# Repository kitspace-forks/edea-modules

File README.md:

# EDeA Test Modules

This is a collection of official modules to try out the functionality of EDeA.
The modules are provided on a best-effort basis and will be documented as verified
if and when they have been used in production boards.

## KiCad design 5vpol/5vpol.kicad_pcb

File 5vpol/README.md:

# 16-V Input 3-A Output Point-of-Load with TPS62135

## Overview

This design is based around the Texas Instruments TPS62135 converter.  
[IC Datasheet](https://www.ti.com/lit/ds/symlink/tps62135.pdf).
For layout, see the .kicad_pcb file in the repository.

## Use

Connect the input side to the power source, and the output side to the load. The converter powers on automatically above 3V input. Output is programmed to 5.0 volt, can be changed by replacing R2 and/or R3. Reference voltage is 0.7 V. Supported input voltage is around 16 V max., above which the D1 TVS diode will start to clamp. You can remove this to increase maximum input voltage to 18V abs max, but then you should avoid hot-plugging the board.

You can shut down the converter while input power is present: Pull EN input low. The EN pin is pulled up on-board to VIN with 10kOhm, therefore the circuit you use to discharge EN must withstand the maximum VIN you plan to apply.

Alternatively, you can disconnect the input.

To achieve 20-ish uA standby current, remove the output indicator LED D2 or its series resistor R6.

This DC/DC can run in 100% duty cycle mode, when the input voltage is lower or equals to the set output voltage.

## Properties

|                          Specifications |                                                                    |
|----------------------------------------:|--------------------------------------------------------------------|
|                             Dimensions: | 25x42x3mm (without pin headers)                                    |
|                                   Mass: | 3.3g                                                               |
|                          Mounting Hole: | M3 at (-6;-4)mm from bottom right corner                           |
|                          Input Voltage: | 3V - 16V                                                           |
|                         Output Voltage: | 5.0V (default)<br>Optionally between 0.8V and 12V                  |
|             Internal Reference Voltage: | 0.7V                                                               |
|                          Output Ripple: | 45mVpp with no load<br>30mVpp in Continuous Conduction Mode        |
|                         Output Current: | 4A peak<br>3.4A continuous                                         |
|                     Maximum Duty Cylce: | 100%                                                               |
|                            Power Stage: | Synchronous buck with nMOS switches                                |
|             Overtemperature Protection: | Yes, at 160 degrees Celsius, with 20 dC hysteresis                 |
|               Short Circuit Protection: | Yes, at 6A                                                         |
|              Fixed Switching Frequency: | No. (default) In Continuous Conduction Mode fSW is approx. 2.5 MHz <br> Yes (pseudo-static around 2.5 MHz) by pulling MODE pin high (VIN tolerant) |
|                             Soft Start: | 25ms, programmed by C3                                             |
| Transient Input Overvoltage Protection: | Yes, with on-board TVS diode                                       |
|          Output Overvoltage Protection: | No.                                                                |
|                       Hot-Plug Capable: | Yes.                                                               |
|                          Soft Shutdown: | Yes (by pulling EN pin low)                                        |
|                    Output ON Indicator: | Yes. (pink LED)                                                    |
|                      Power Good Output: | Yes.                                                               |
|                                   RoHS: | Yes, plus tantalum-free.                                           |

## Test report

I spent half a year validating this IC design before it was released to the market, and it is very robust. The only way to kill it is through overvoltage on its input or its output (or maybe using the wrong inductor and saturating it, but I have not tried that; it still works down to 0.7 uH).

Current limit is robust, and it also limits negative current when run in FPWM mode (MODE=high, see JP1) to around 1A. You can use it as a rudimentary bidirectional buck-boost if you so please!

You can even use it as an inverting buck-boost converter! (connect GND to the pin labeled VOUT, VIN is VIN, GND is -Vout) Mind that in this setup Vin+abs(Vout) still can't be higher than 17V!

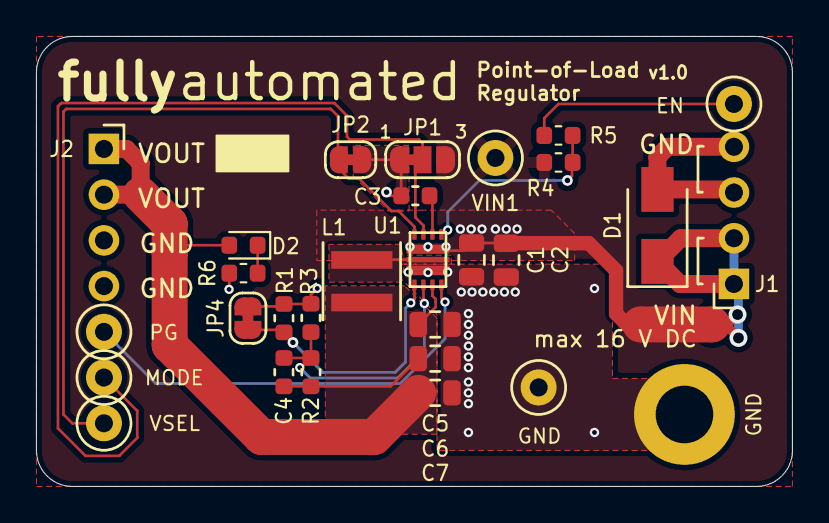
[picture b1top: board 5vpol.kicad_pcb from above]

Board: 2 copper layers, 42.0 x 25.0 mm, 31 parts (1 on the bottom side), 14 nets.

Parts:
C1, C2: 2.2uF/25V; C_0805_2012Metric
C3: 100nF/25V; C_0603_1608Metric
C4: 22pF/50V; C_0603_1608Metric
C5, C6, C7: 10uF/6.3V; C_0805_2012Metric
D1: SMAJ15A-13-F; D_SMA
D2: LED_Small_ALT; LED_0603_1608Metric
EN: EN; TestPoint_Loop_D1.80mm_Drill1.0mm_Beaded
G1: Fully_Automated_Logo; fully_automated_logo_soldermask
H1: MountingHole_Pad; MountingHole_3.2mm_M3_DIN965_Pad
J1: IN; PinSocket_1x04_P2.54mm_Horizontal
J2: OUT; PinSocket_1x04_P2.54mm_Horizontal
JP1: SolderJumper_3_Bridged12; SolderJumper-3_P1.3mm_Bridged12_RoundedPad1.0x1.5mm_NumberL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
JP2, JP4: SolderJumper_2_Bridged; SolderJumper-2_P1.3mm_Bridged_RoundedPad1.0x1.5mm
L1: XGL4020-102ME_; L_Coilcraft_XxL4020
MODE1: MODE; TestPoint_Loop_D1.80mm_Drill1.0mm_Beaded
NT1: Net-Tie_2; NetTie-2_SMD_Pad2.0mm
PG1: PG; TestPoint_Loop_D1.80mm_Drill1.0mm_Beaded
R1: dnp; R_0603_1608Metric
R2: 240k; R_0603_1608Metric
R3: 39k; R_0603_1608Metric
R4: 10k; R_0603_1608Metric
R5: 100; R_0603_1608Metric
R6: 2k2; R_0603_1608Metric
TP1: GND; TestPoint_Loop_D1.80mm_Drill1.0mm_Beaded
U1: TPS62135; RGX_TI_VQFN-HR11
VIN1: VIN; TestPoint_Loop_D1.80mm_Drill1.0mm_Beaded
VSEL1: VSEL; TestPoint_Loop_D1.80mm_Drill1.0mm_Beaded

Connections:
+5V: C4.1, C5.1, C6.1, C7.1, D2.2, J2.1, J2.2, L1.2, R2.1, U1.6
/TPS62135 Power Supply/FB: C4.2, R2.2, R3.1, U1.5
/TPS62135 Power Supply/MODE: JP1.2, MODE1.1, U1.10
/TPS62135 Power Supply/PGOOD: PG1.1, U1.7
/TPS62135 Power Supply/SW: L1.1, U1.2
GND: C1.2, C2.2, C3.2, C5.2, C6.2, C7.2, D1.2, H1.1, J1.3, J1.4, J2.3, J2.4, JP1.1, JP2.1, JP4.2, R1.2, R3.2, R6.2, TP1.1, U1.3
unnamed: C1.1, C2.1, JP1.3, NT1.2, R4.2, U1.1, VIN1.1
unnamed: C3.1, U1.9
unnamed: D2.1, R6.1
unnamed: EN.1, R5.1
unnamed: JP2.2, U1.11, VSEL1.1
unnamed: JP4.1, R1.1, U1.4
unnamed: R4.1, R5.2, U1.8
VBUS: D1.1, J1.1, J1.2, NT1.1

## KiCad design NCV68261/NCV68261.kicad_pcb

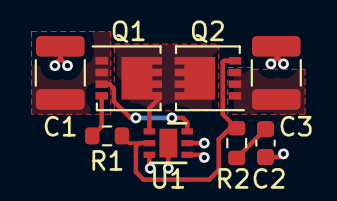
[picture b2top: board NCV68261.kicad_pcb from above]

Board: 2 copper layers, 8 parts (0 on the bottom side), 7 nets.

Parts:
C1, C3: 10uF/63V; C_1210_3225Metric
C2: 1nF; C_0603_1608Metric
Q1, Q2: DMT6007LFG-7; Diodes_PowerDI3333-8
R1, R2: 10R; R_0603_1608Metric
U1: NCV68261; DFN-6-1EP_2x2mm_P0.65mm_EP1x1.6mm

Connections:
/V_{BUS}: C1.1, Q1.1 (S), Q1.2 (S), Q1.3 (S), U1.6 (IN)
/V_{PROT}: C3.1, Q2.1 (S), Q2.2 (S), Q2.3 (S)
GND: C1.2, C2.1, C3.2, U1.3 (D), U1.5 (GND), U1.7
unnamed: C2.2, R2.2
unnamed: Q1.4 (G), R1.1
unnamed: Q1.5 (D), Q2.5 (D), U1.1 (S)
unnamed: Q2.4 (G), R1.2, R2.1, U1.2 (G)

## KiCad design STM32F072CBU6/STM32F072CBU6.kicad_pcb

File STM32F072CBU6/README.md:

# STM32CBU6

This module provides the STM32F072 in a 48-Pin VQFN package.

## Datasheets

- [STM32F072CB](https://www.st.com/resource/en/datasheet/stm32f072cb.pdf)
- [Reference Manual](https://www.st.com/resource/en/reference_manual/dm00031936-stm32f0x1stm32f0x2stm32f0x8-advanced-armbased-32bit-mcus-stmicroelectronics.pdf)

## Routing

No special assumptions, except for the existance of a Ground-plane, were made. The 3V3 rail was routed
without a 3V3 plane in mind in case this gets used in a more constrained setup.

## Debug Connector

The footprint for a TC2030 connector is present for debugging-purposes.

## JLC Compatible

All parts, except the STM32F072 are basic parts and have been choosen to be compatible
with the Microcontroller.

## Tolerances, Traces & Vias

Trace widths, Vias and spacing are compatible with 2oz outer layer on with common tolerances.
If lower tolerances are available, the traces and caps can be moved around still to make it
a bit more compact.

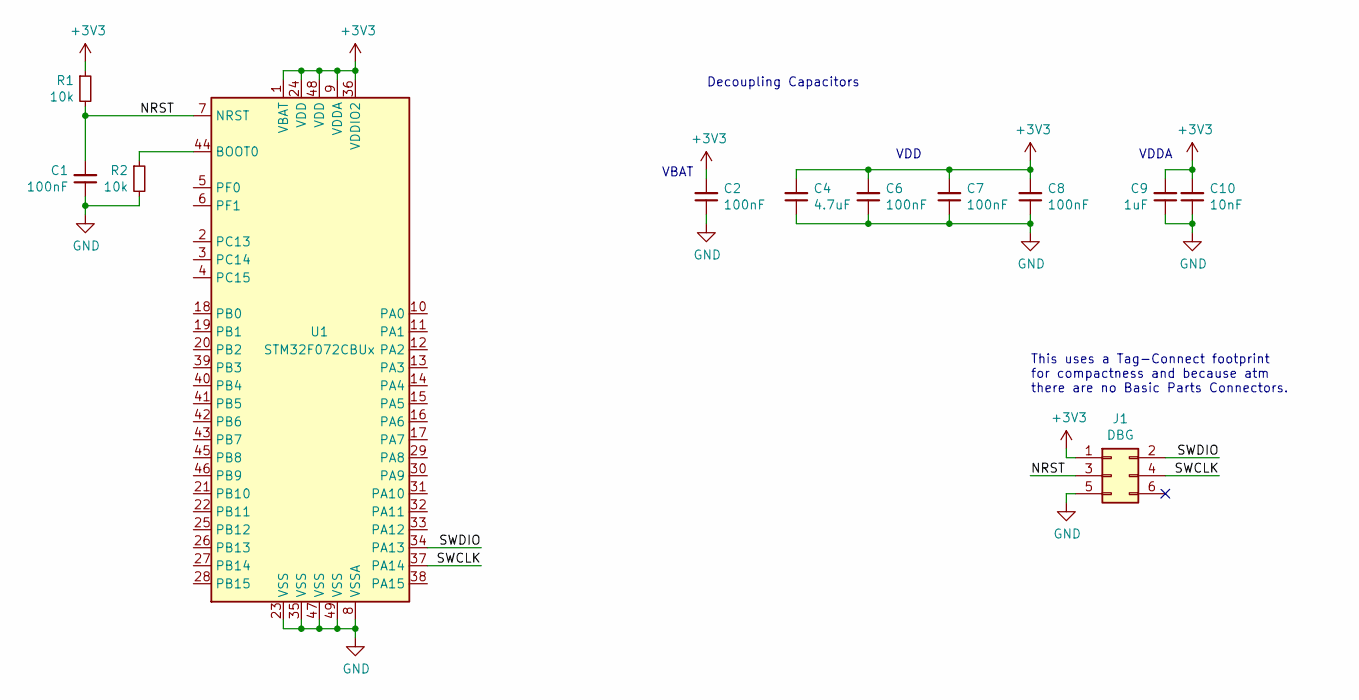
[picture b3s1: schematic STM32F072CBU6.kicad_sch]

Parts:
C1, C2, C6, C7, C8: 100nF; C_0402_1005Metric; JLC 0402
C4: 4.7uF; C_0402_1005Metric; JLC 0402
C9: 1uF; C_0402_1005Metric; JLC 0402
C10: 10nF; C_0402_1005Metric; JLC 0402
J1: DBG; Tag-Connect_TC2030-IDC-NL_2x03_P1.27mm_Vertical; MPN DNP
R1, R2: 10k; R_0402_1005Metric; JLC 0402
U1: STM32F072CBUx; QFN-48-1EP_7x7mm_P0.5mm_EP5.6x5.6mm; JLC UFQFPN-48_EP_7.0x7.0x0.5P

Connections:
+3V3: C2.2, C4.2, C6.2, C7.2, C8.2, C9.2, C10.2, J1.1, R1.1, U1.1 (VBAT), U1.9 (VDDA), U1.24 (VDD), U1.36 (VDDIO2), U1.48 (VDD)
/NRST: C1.2, J1.3, R1.2, U1.7 (NRST)
/SWCLK: J1.4, U1.37 (PA14)
/SWDIO: J1.2, U1.34 (PA13)
GND: C1.1, C2.1, C4.1, C6.1, C7.1, C8.1, C9.1, C10.1, J1.5, R2.2, U1.8 (VSSA), U1.23 (VSS), U1.35 (VSS), U1.47 (VSS), U1.49 (VSS)
unnamed: R2.1, U1.44 (BOOT0)

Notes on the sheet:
VDD
This uses a Tag-Connect footprint for compactness and because atm there are no Basic Parts Connectors.
VBAT
VDDA
Decoupling Capacitors

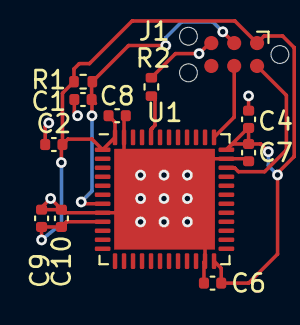
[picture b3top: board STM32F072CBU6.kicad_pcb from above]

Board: 2 copper layers, 12 parts (0 on the bottom side), 6 nets.

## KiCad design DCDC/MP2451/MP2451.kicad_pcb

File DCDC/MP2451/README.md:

# MP2451

This is an asynchronous buck module which supports up to 36V Vin and is configured for 3.3V out.

## JLC Compatible

All parts except the inductor are JLC basic parts.

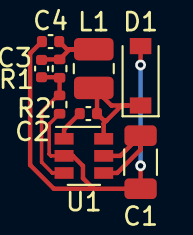
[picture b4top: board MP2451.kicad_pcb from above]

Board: 2 copper layers, 9 parts (0 on the bottom side), 6 nets.

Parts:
C1: 10uF; C_1206_3216Metric
C2: 100nF; C_0402_1005Metric
C3: 33pF; C_0402_1005Metric
C4: 10uF; C_0402_1005Metric
D1: 40V; D_SOD-123
L1: 2.2uH; L_1008_2520Metric
R1: 75k; R_0402_1005Metric
R2: 24k; R_0402_1005Metric
U1: MP2451; SOT-23-6

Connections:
+3V3: C3.2, C4.2, L1.2, R1.1
/FB: C3.1, R1.2, R2.1, U1.3
GND: C1.1, C4.1, D1.2, R2.2, U1.2
unnamed: C2.1, D1.1, L1.1, U1.6
unnamed: C2.2, U1.1
VBUS: C1.2, U1.4, U1.5

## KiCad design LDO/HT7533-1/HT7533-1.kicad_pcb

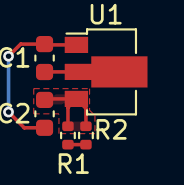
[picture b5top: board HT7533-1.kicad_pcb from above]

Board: 2 copper layers, 5 parts (0 on the bottom side), 4 nets.

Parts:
C1, C2: 10uF; C_0603_1608Metric
R1, R2: 1; R_0402_1005Metric
U1: HT75xx-1-SOT89; SOT-89-3

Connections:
+3V3: R1.1, R2.1
GND: C1.2, C2.2, U1.1
unnamed: C2.1, R1.2, R2.2, U1.3
VBUS: C1.1, U1.2

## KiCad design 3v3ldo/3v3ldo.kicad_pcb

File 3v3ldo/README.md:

# A simple 3.3-V LDO

TODO: add some description

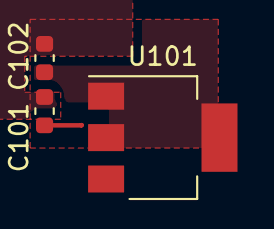
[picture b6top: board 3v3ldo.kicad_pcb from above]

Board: 2 copper layers, 3 parts (0 on the bottom side), 3 nets.

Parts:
C101, C102: 1uF; C_0603_1608Metric
U101: NCP1117-3.3_SOT223; SOT-223-3_TabPin2

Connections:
/GND: C101.2, C102.2, U101.1
/VIN: C101.1, U101.3
/VOUT: C102.1, U101.2

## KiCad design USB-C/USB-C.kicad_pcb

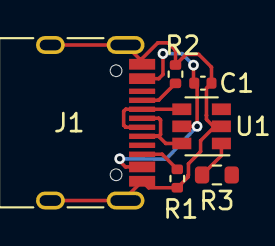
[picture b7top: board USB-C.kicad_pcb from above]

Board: 2 copper layers, 6 parts (0 on the bottom side), 7 nets.

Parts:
C1: 100nF; C_0402_1005Metric
J1: USB_C_Receptacle_USB2.0; USB_C_Receptacle_HRO_TYPE-C-31-M-12
R1, R2: 5.1k; R_0402_1005Metric
R3: 1.5k; R_0603_1608Metric
U1: USBLC6-2SC6; SOT-23-6

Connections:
/D+: R3.2, U1.1
/USB_D+: J1.A6, J1.B6, U1.6
/USB_D-: J1.A7, J1.B7, U1.4
GND: C1.2, J1.A1, J1.A12, J1.B1, J1.B12, J1.S1, R1.2, R2.2, U1.2
unnamed: J1.A5, R2.1
unnamed: J1.B5, R1.1
VBUS: C1.1, J1.A4, J1.A9, J1.B4, J1.B9, U1.5

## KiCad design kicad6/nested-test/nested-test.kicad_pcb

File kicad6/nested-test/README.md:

Just a Nested Schematic Test

How to find UUIDs:
`grep -horP '[0-9a-f]{8}-[0-9a-f]{4}-[0-9a-f]{4}-[0-9a-f]{4}-[0-9a-f]{12}' * | sort | uniq -c | sort -n`

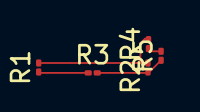
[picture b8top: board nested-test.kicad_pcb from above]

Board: 2 copper layers, 5 parts (0 on the bottom side), 4 nets.

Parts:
R1, R2: 666; R_01005_0402Metric
R3: 0; R_01005_0402Metric
R4: 123; R_01005_0402Metric
R5: 3; R_01005_0402Metric

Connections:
/subsheet1/pin1: R2.1, R3.2, R5.1
/subsheet2/pin1: R4.1, R5.2
/subsheet/pin1: R1.1, R3.1
global-pin: R1.2, R2.2, R4.2

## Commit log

2021-04-16 Initial commit of test projects
2021-04-16 Update readmes
2021-04-22 Add GD32E103CBT6 module
2021-04-22 Provide the right readme filename
2021-04-22 Use absolute URL to gitlab for images
2021-04-22 Add a USB-C receptacle module
2021-04-22 Add top-level readme
2021-04-23 Add two new modules
2021-04-23 Actually add all the files
2021-04-24 Add a STM32F072CBU6 module
2021-04-24 Fix a tpyo
2021-05-29 Move things around a little bit
2021-12-21 added kicad-6 converted test modules
2021-12-21 added nested schematic test
2021-12-21 added gitignore, removed backups
2021-12-21 removed prl file
2021-12-21 added grep regex to readme for future reference
2021-12-21 added empty files for reference
2022-05-08 update files to kicad 6
2022-07-04 remove test string again
2022-07-04 add example book
2022-08-28 add params to edea.yml
2022-08-28 fix param definition
2022-09-03 NVC68261 reverse-polarity prot, high-side-switch
2022-09-03 use smaller fets
2022-09-18 name typo in NCV68261
2022-10-16 add a better test report for 5vpol
2023-08-15 Add `description` and `category` keys to manifest
2024-02-18 Update modules to kicad v7 format
2024-02-18 update LDO to kicad v7 format
2024-02-19 Revert "Update modules to kicad v7 format"
    This reverts commit 3325eb02d48d3d222bc7f8945228a1814ae85736.
2024-02-19 Reapply "Update modules to kicad v7 format"
    This reverts commit fa5cc85431189ac7a3beedf0871b5723203ae43f.
2024-06-23 Fix broken links and images
